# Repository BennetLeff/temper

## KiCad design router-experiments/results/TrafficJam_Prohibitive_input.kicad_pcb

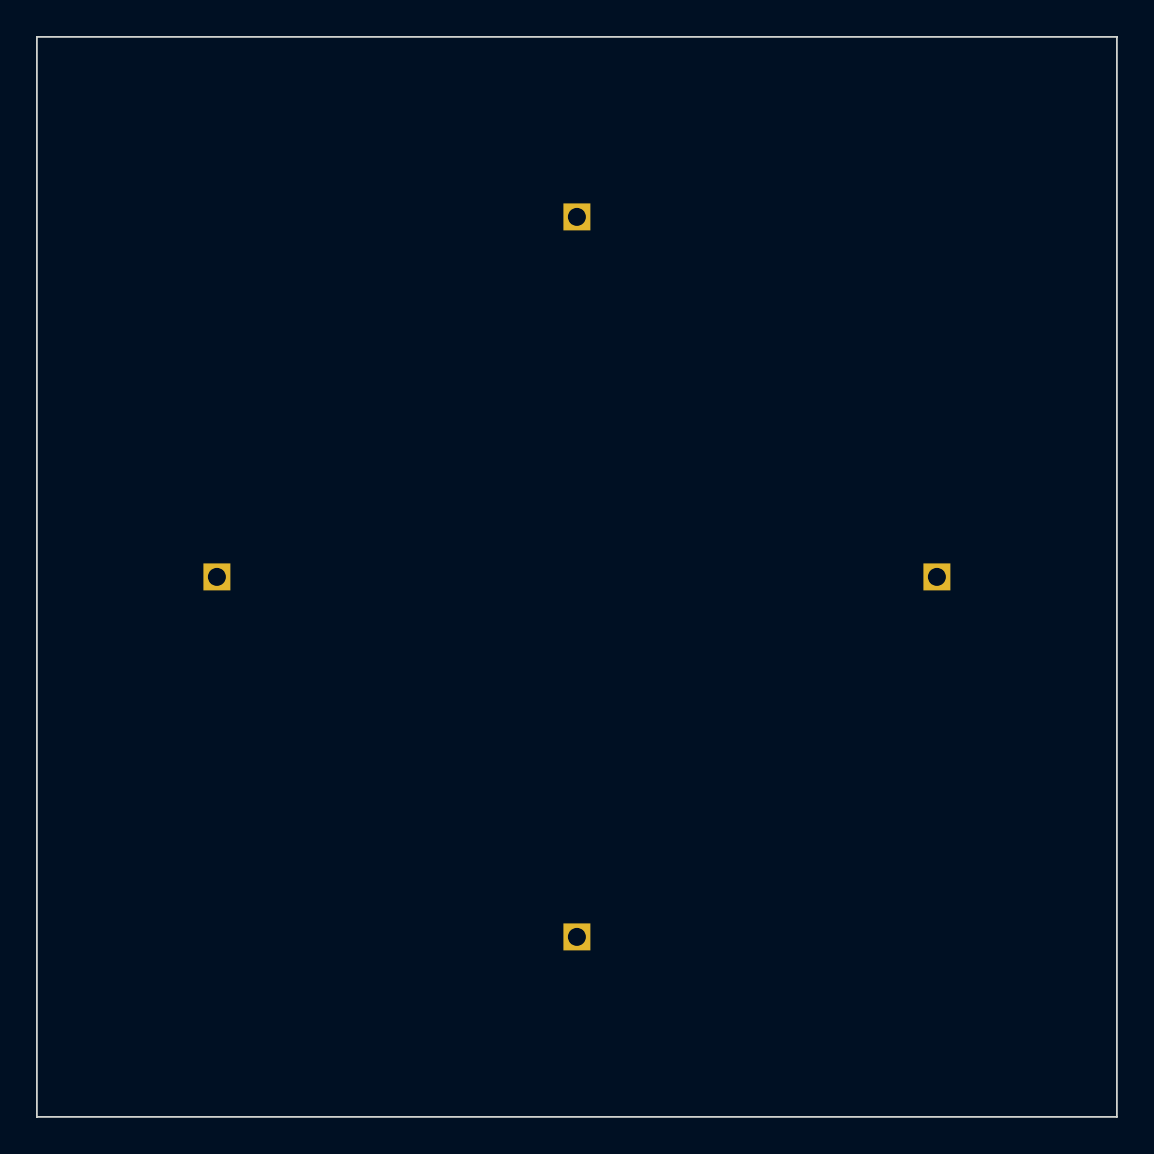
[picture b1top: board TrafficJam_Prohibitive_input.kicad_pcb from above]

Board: 2 copper layers, 60.0 x 60.0 mm, 4 parts (0 on the bottom side), 2 nets, no tracks yet.

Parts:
J_E: Conn_1; Header_1pin_P2.54mm
J_N: Conn_1; Header_1pin_P2.54mm
J_S: Conn_1; Header_1pin_P2.54mm
J_W: Conn_1; Header_1pin_P2.54mm

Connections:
NET_NS: J_N.1, J_S.1
NET_WE: J_E.1, J_W.1

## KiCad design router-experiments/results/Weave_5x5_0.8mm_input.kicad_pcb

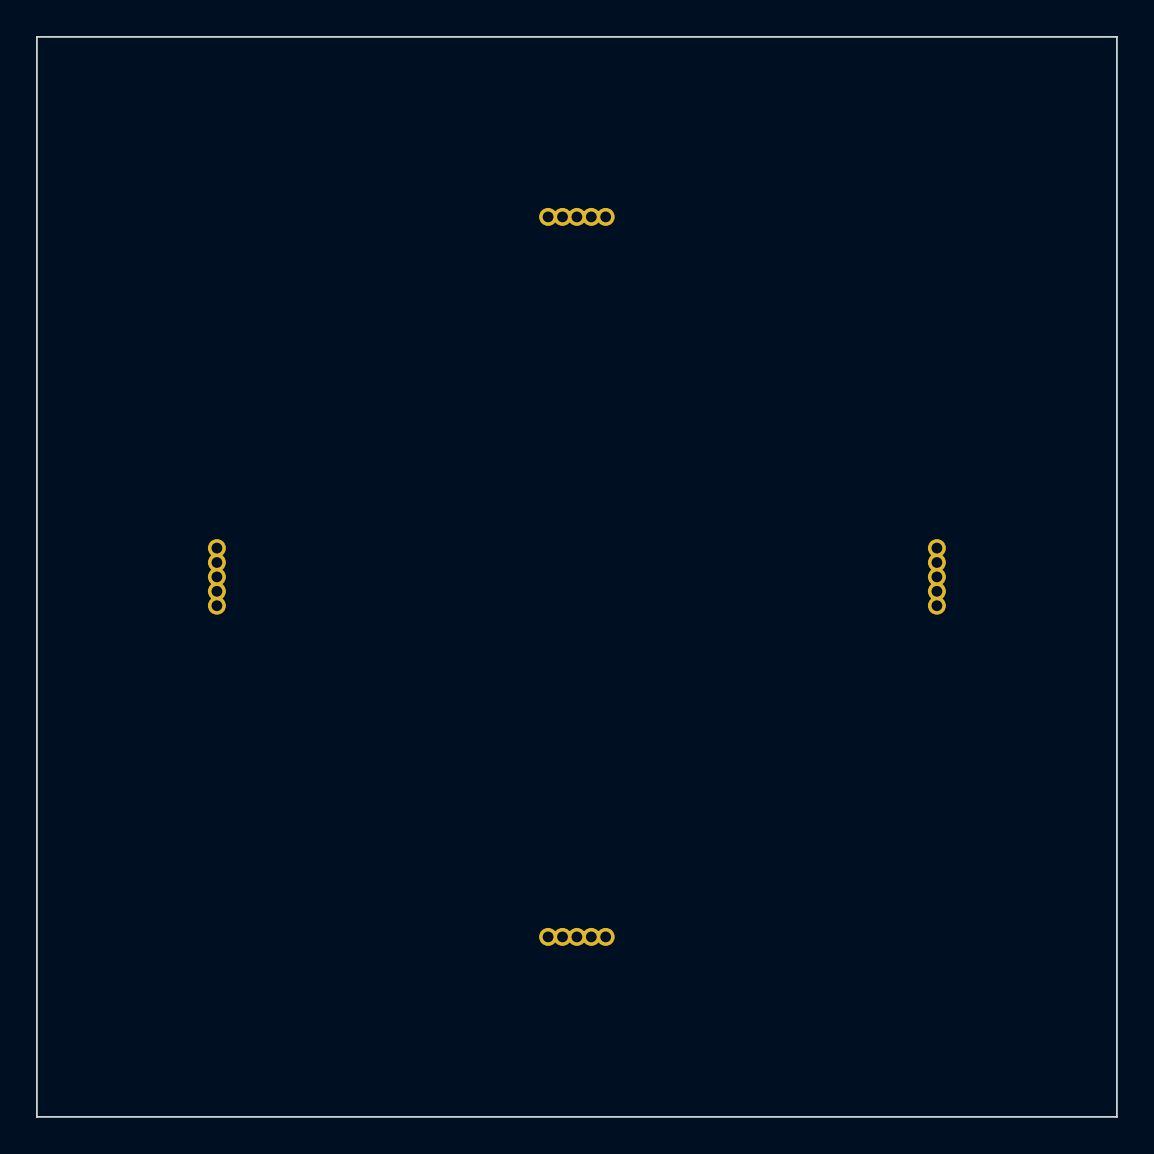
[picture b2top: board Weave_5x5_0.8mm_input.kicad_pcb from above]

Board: 2 copper layers, 60.0 x 60.0 mm, 20 parts (0 on the bottom side), 10 nets, no tracks yet.

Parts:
JH_E_0, JH_E_1, JH_E_2, JH_E_3, JH_E_4: Pin
JH_W_0, JH_W_1, JH_W_2, JH_W_3, JH_W_4: Pin
JV_N_0, JV_N_1, JV_N_2, JV_N_3, JV_N_4: Pin
JV_S_0, JV_S_1, JV_S_2, JV_S_3, JV_S_4: Pin

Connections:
H_0: JH_E_0.1, JH_W_0.1
H_1: JH_E_1.1, JH_W_1.1
H_2: JH_E_2.1, JH_W_2.1
H_3: JH_E_3.1, JH_W_3.1
H_4: JH_E_4.1, JH_W_4.1
V_0: JV_N_0.1, JV_S_0.1
V_1: JV_N_1.1, JV_S_1.1
V_2: JV_N_2.1, JV_S_2.1
V_3: JV_N_3.1, JV_S_3.1
V_4: JV_N_4.1, JV_S_4.1
